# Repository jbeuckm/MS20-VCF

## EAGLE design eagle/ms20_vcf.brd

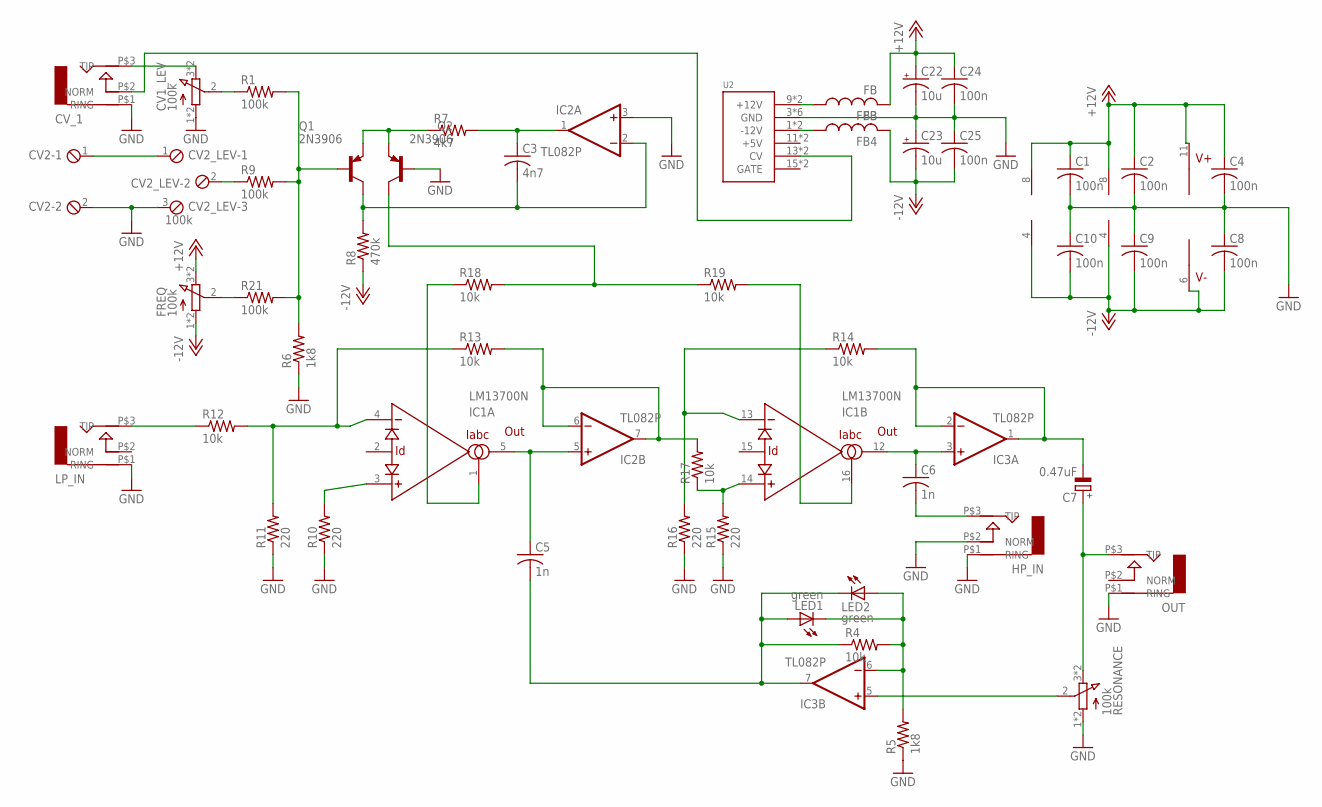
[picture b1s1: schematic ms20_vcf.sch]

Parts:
C1, C2, C4, C8, C9, C10: 100n; C1206
C3: 4n7; C050-024X044
C5, C6: 1n; C050-024X044
C7: 0.47uF; B45181A
C22, C23: 10u; B45181A
C24, C25: 100n; C050-024X044
CV1_LEV: 100k; 3RP/1610N
CV2: MPT2; 2POL254
CV2_LEV: 100k; 3POL254
CV_1: AUDIO-JACKITEAD; JACK-90DEG-ITEAD
FB3, FB4: FB
FREQ: 100k; 3RP/1610N
HP_IN: AUDIO-JACKITEAD; JACK-90DEG-ITEAD
IC1: LM13700N; DIL16
IC2, IC3: TL082P; DIL08
LED1, LED2: green; LED5MM
LP_IN: AUDIO-JACKITEAD; JACK-90DEG-ITEAD
OUT: AUDIO-JACKITEAD; JACK-90DEG-ITEAD
Q1, Q2: 2N3906; TO92
R1, R9, R21: 100k; 0207/7
R4, R12, R13, R14, R17, R18, R19: 10k; 0207/7
R5, R6: 1k8; 0207/7
R7: 4k7; 0207/7
R8: 470k; 0207/7
R10, R11, R15, R16: 220; 0207/7
RESONANCE: 100k; 3RP/1610N
U2: POWER; POWER_16

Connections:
+12V: C1.1, C2.1, C4.1, C22.+, C24.1, FB3.P$2 (2), FREQ.3 (E), FREQ.6 (E), IC1.11 (V+), IC2.8 (V+), IC3.8 (V+)
-12V: C8.2, C9.2, C10.2, C23.-, C25.2, FB4.P$2 (2), FREQ.1 (A), FREQ.4 (A), IC1.6 (V-), IC2.4 (V-), IC3.4 (V-), R8.1
GND: C1.2, C2.2, C4.2, C8.1, C9.1, C10.1, C22.-, C23.+, C24.2, C25.1, CV1_LEV.1 (A), CV1_LEV.4 (A), CV2.2, CV2_LEV.3, CV_1.P$1 (RING), HP_IN.P$1 (RING), HP_IN.P$2 (NORM), IC2.3 (+IN), LP_IN.P$1 (RING), OUT.P$1 (RING), Q2.2 (B), R5.1, R6.1, R10.1, R11.1, R15.1, R16.1, RESONANCE.1 (A), RESONANCE.4 (A), U2.3 (GND), U2.4 (GND), U2.5 (GND), U2.6 (GND), U2.7 (GND), U2.8 (GND)
unnamed: IC3.6 (-IN), LED1.K (C), LED2.A, R4.2, R5.2
unnamed: C5.2, IC3.7 (OUT), LED1.A, LED2.K (C), R4.1
unnamed: C3.2, IC2.2 (-IN), Q1.1 (C), R8.2
unnamed: C3.1, IC2.1 (OUT), R7.2
unnamed: Q1.3 (E), Q2.3 (E), R7.1
unnamed: IC3.5 (+IN), RESONANCE.2 (S)
unnamed: CV1_LEV.2 (S), R1.1
unnamed: CV2_LEV.2, R9.1
unnamed: C5.1, IC1.5 (OUT), IC2.5 (+IN)
unnamed: C6.1, IC1.12 (OUT), IC3.3 (+IN)
unnamed: C7.-, IC3.1 (OUT), IC3.2 (-IN), R14.2
unnamed: C7.+, OUT.P$3 (TIP), RESONANCE.3 (E), RESONANCE.6 (E)
unnamed: IC1.1 (IABC), R18.1
unnamed: IC1.4 (-IN), R11.2, R12.2, R13.1
unnamed: IC1.3 (+IN), R10.2
unnamed: Q2.1 (C), R18.2, R19.1
unnamed: IC1.16 (IABC), R19.2
unnamed: IC1.13 (-IN), R14.1, R16.2
unnamed: IC2.6 (-IN), IC2.7 (OUT), R13.2, R17.2
unnamed: IC1.14 (+IN), R15.2, R17.1
unnamed: Q1.2 (B), R1.2, R6.2, R9.2, R21.2
unnamed: FREQ.2 (S), R21.1
unnamed: CV2.1, CV2_LEV.1
unnamed: CV1_LEV.3 (E), CV1_LEV.6 (E), CV_1.P$3 (TIP)
unnamed: LP_IN.P$3 (TIP), R12.1
unnamed: C6.2, HP_IN.P$3 (TIP)
unnamed: CV_1.P$2 (NORM), U2.13 (CV), U2.14 (CV)
unnamed: FB3.P$1 (1), U2.9 (+12V), U2.10 (+12V)
unnamed: FB4.P$1 (1), U2.1 (-12V), U2.2 (-12V)

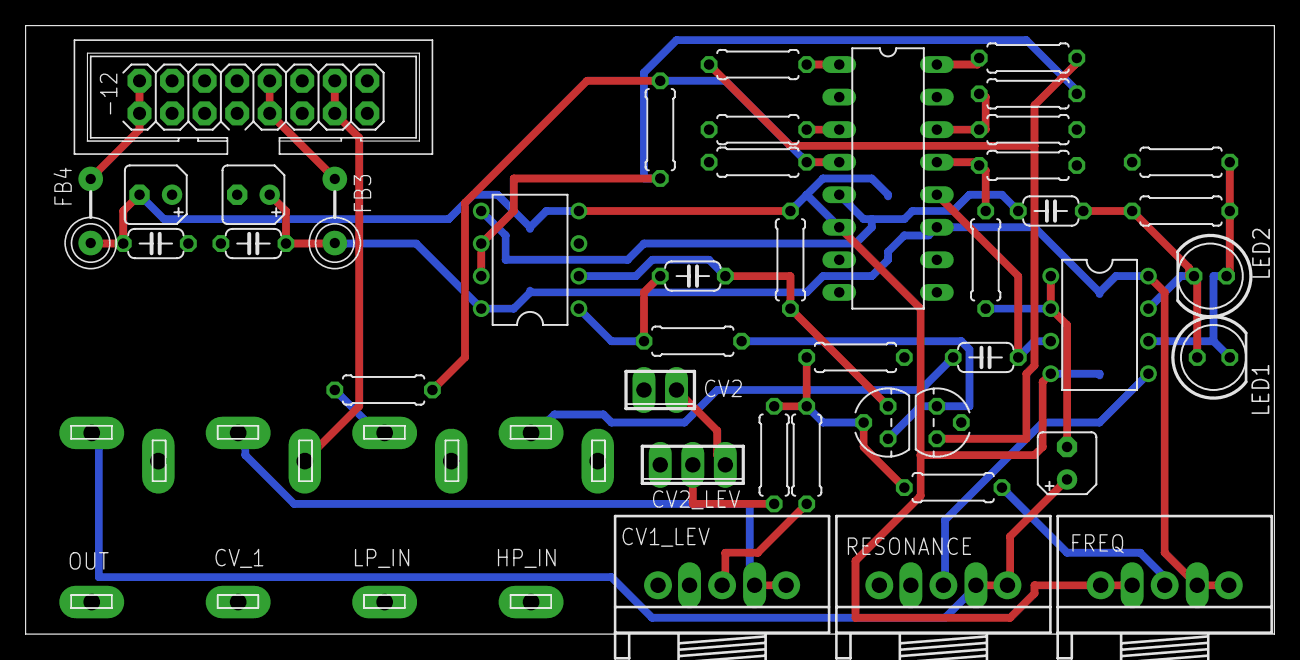
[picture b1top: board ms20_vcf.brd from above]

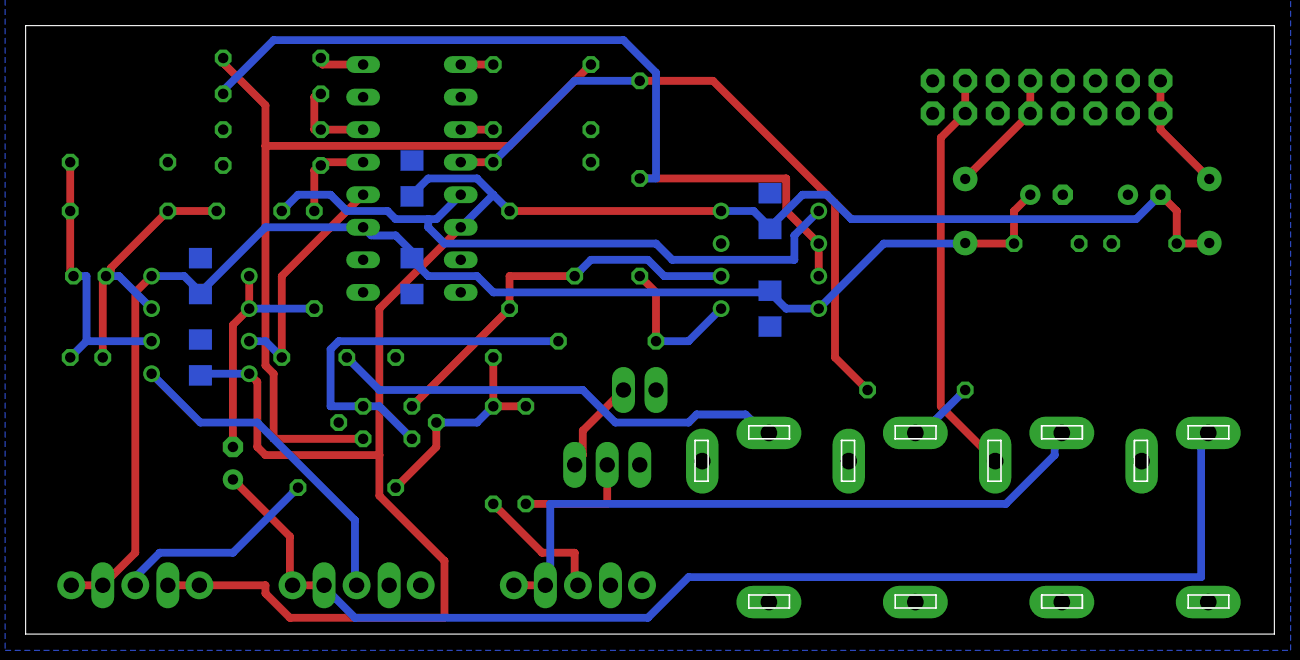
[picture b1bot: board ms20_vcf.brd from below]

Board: 2 copper layers, 97.3 x 47.4 mm, 51 parts (6 on the bottom side), 32 nets.

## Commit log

2015-11-27 all but jacks complete
2015-11-27 jacks
2015-11-27 started on board
2015-11-27 worked on bd
2015-11-28 toward routes
2015-11-28 routed
2015-11-28 rerouted and milling
2015-11-29 burned and works
2015-11-29 panel design
2016-01-05 panel
2017-09-04 began changes for itead
2017-09-04 decoupling caps
2017-09-04 parts on the board
2017-09-05 labels adjusted for visibility
2017-09-05 reordered pots and jacks
2017-09-05 slightly shallower
